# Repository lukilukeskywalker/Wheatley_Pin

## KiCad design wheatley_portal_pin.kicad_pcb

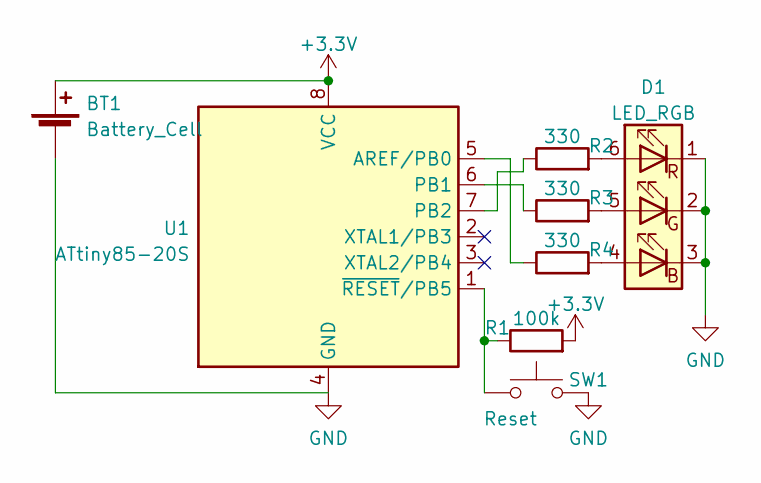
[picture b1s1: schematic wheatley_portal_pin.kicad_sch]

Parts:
BT1: Battery_Cell; LINX CR2032 Holder
D1: LED_RGB; LED_WS2812_PLCC6_5.0x5.0mm_P1.6mm
R1: 100k; R_1206_3216Metric_Pad1.30x1.75mm_HandSolder
R2, R3, R4: 330; R_1206_3216Metric_Pad1.30x1.75mm_HandSolder
SW1: Reset
U1: ATtiny85-20S; SOIC-8W_5.3x5.3mm_P1.27mm

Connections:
+3V3: BT1.1 (+), R1.2, U1.8 (VCC)
GND: BT1.2 (-), D1.1 (RK), D1.2 (GK), D1.3 (BK), SW1.2, U1.4 (GND)
unnamed: D1.4 (BA), R4.2
unnamed: D1.5 (GA), R3.2
unnamed: D1.6 (RA), R2.2
unnamed: R1.1, SW1.1, U1.1 (~RESET/PB5)
unnamed: R2.1, U1.7 (PB2)
unnamed: R3.1, U1.6 (PB1)
unnamed: R4.1, U1.5 (AREF/PB0)

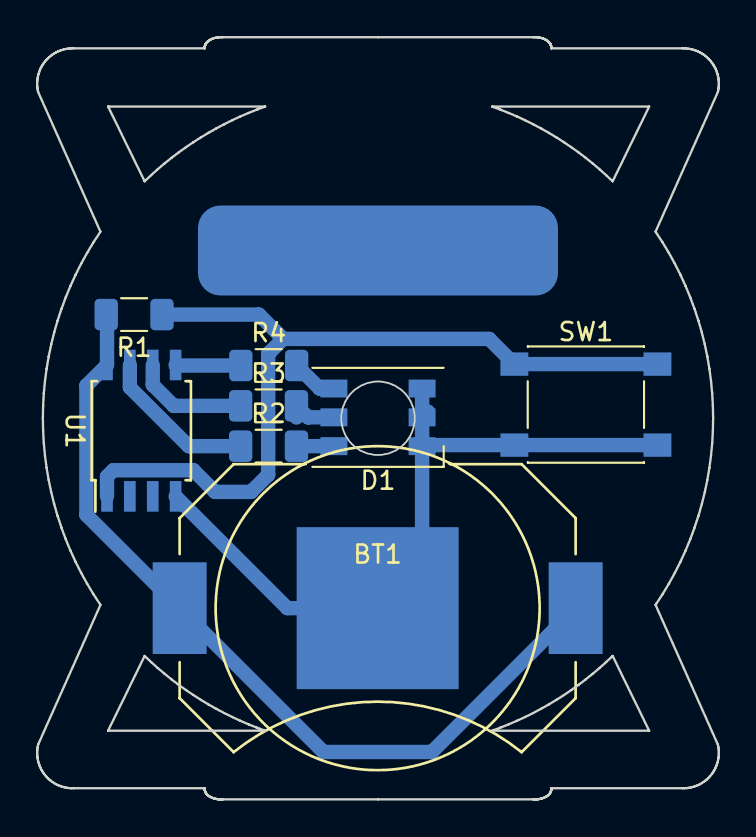
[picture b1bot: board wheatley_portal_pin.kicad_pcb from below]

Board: 2 copper layers, 37.9 x 42.3 mm, 8 parts (8 on the bottom side), 9 nets.

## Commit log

2022-12-13 [Schematic][Board][Code]Initial Commit
2023-11-28 [?]Bunch of stuff
